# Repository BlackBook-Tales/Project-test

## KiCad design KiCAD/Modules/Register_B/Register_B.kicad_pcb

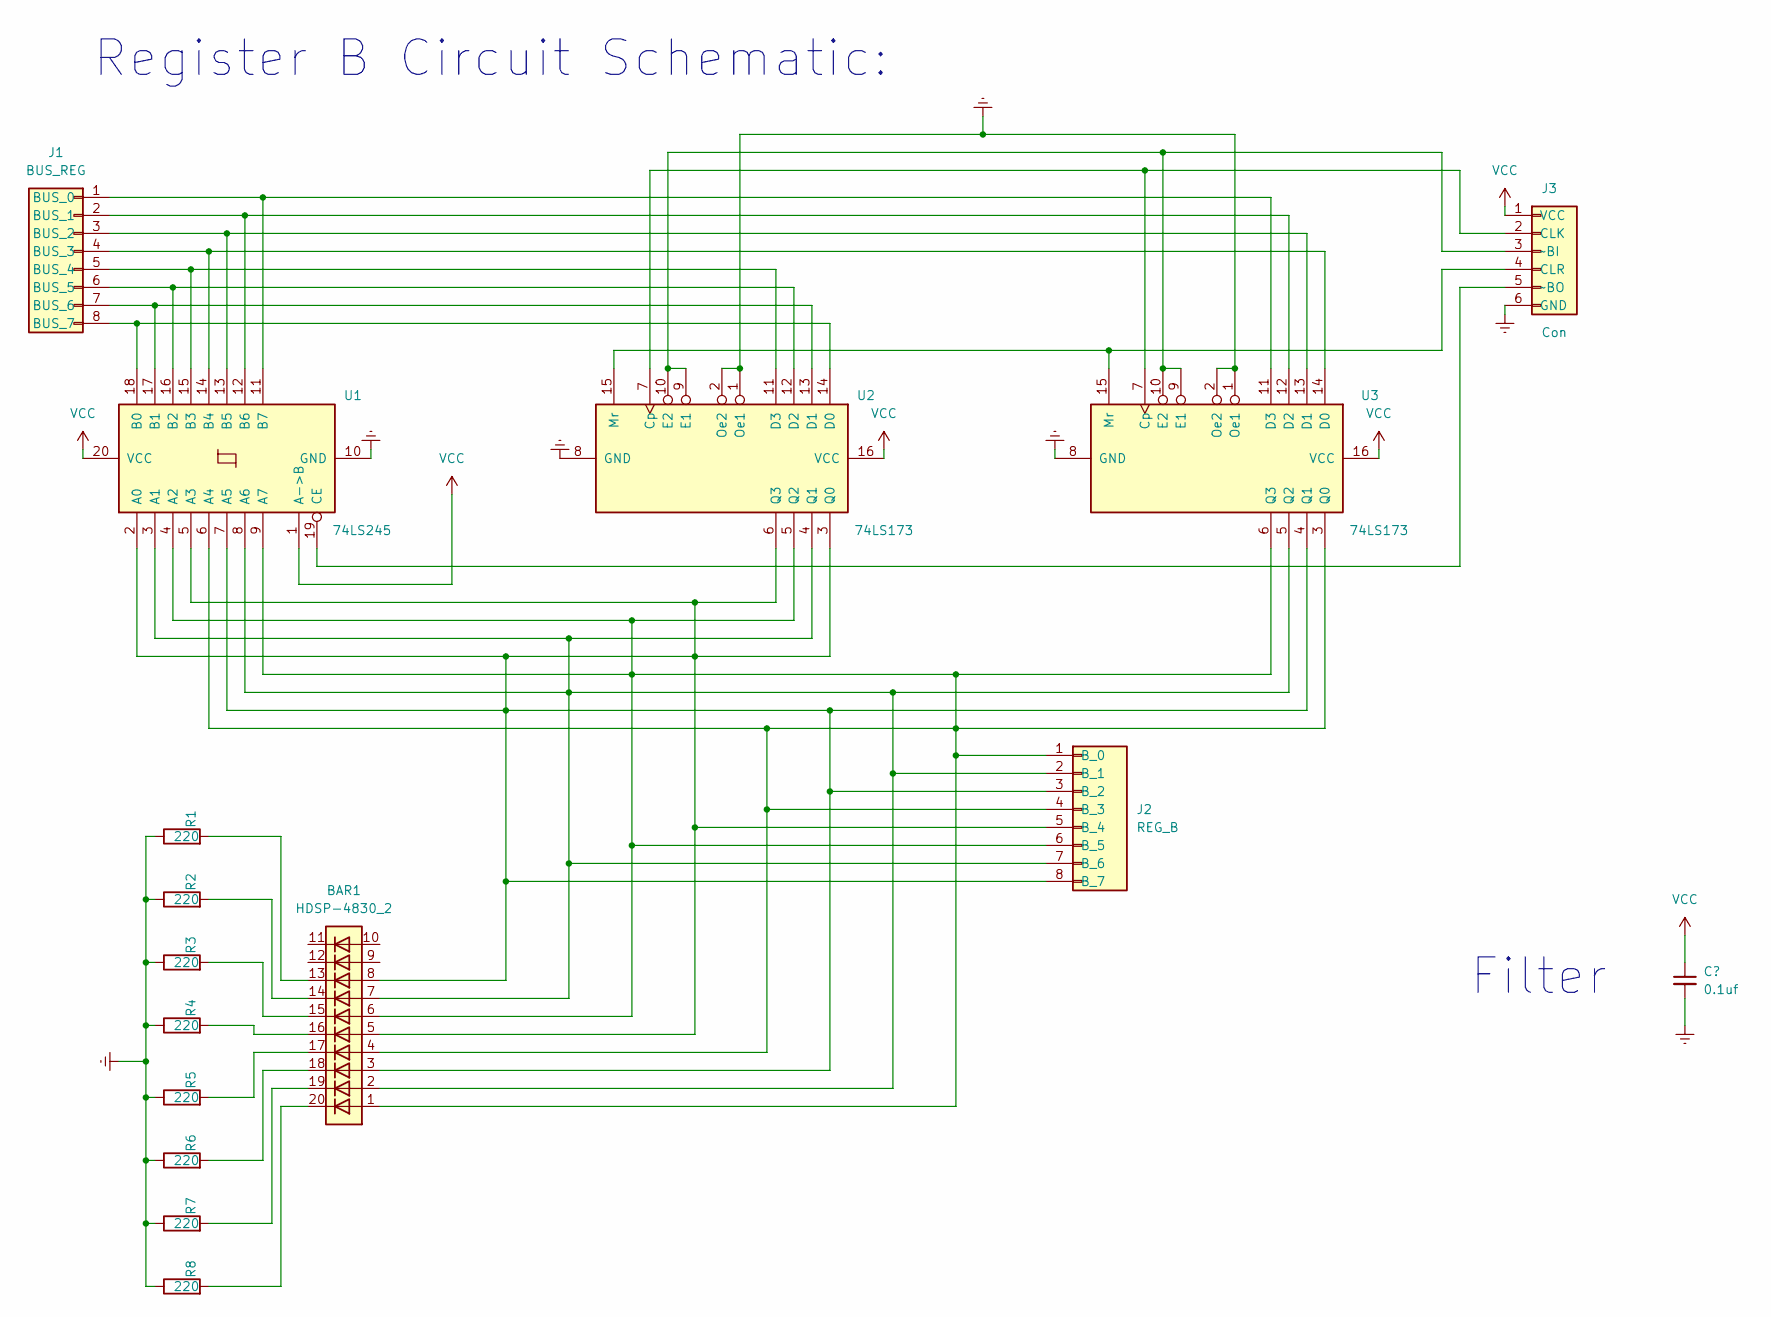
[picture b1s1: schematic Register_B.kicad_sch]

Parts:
BAR1: HDSP-4830_2; HDSP-4830
J1: BUS_REG; PinHeader_1x08_P1.00mm_Vertical
J2: REG_B; PinHeader_1x08_P1.00mm_Vertical
J3: Con; PinHeader_1x06_P1.00mm_Vertical
R1, R2, R3, R4, R5, R6, R7, R8: 220; R_Axial_DIN0204_L3.6mm_D1.6mm_P5.08mm_Horizontal
U1: 74LS245; DIP-20_W7.62mm
U2, U3: 74LS173; DIP-16_W7.62mm

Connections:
Earth: J3.6 (GND), R1.1, R2.1, R3.1, R4.1, R5.1, R6.1, R7.1, R8.1, U1.10 (GND), U2.1 (Oe1), U2.2 (Oe2), U2.8 (GND), U3.1 (Oe1), U3.2 (Oe2), U3.8 (GND)
unnamed: BAR1.1 (A), BAR1.4 (A), BAR1.6 (A), J2.1 (B_0), J2.4 (B_3), J2.6 (B_5), U1.4 (A2), U1.6 (A4), U1.9 (A7), U2.5 (Q2), U3.3 (Q0), U3.6 (Q3)
unnamed: BAR1.2 (A), BAR1.7 (A), J2.2 (B_1), J2.7 (B_6), U1.3 (A1), U1.8 (A6), U2.4 (Q1), U3.5 (Q2)
unnamed: BAR1.3 (A), BAR1.5 (A), BAR1.8 (A), J2.3 (B_2), J2.5 (B_4), J2.8 (B_7), U1.2 (A0), U1.5 (A3), U1.7 (A5), U2.3 (Q0), U2.6 (Q3), U3.4 (Q1)
unnamed: BAR1.13 (K), R1.2
unnamed: BAR1.14 (K), R2.2
unnamed: BAR1.15 (K), R3.2
unnamed: BAR1.16 (K), R4.2
unnamed: BAR1.17 (K), R5.2
unnamed: BAR1.18 (K), R6.2
unnamed: BAR1.19 (K), R7.2
unnamed: BAR1.20 (K), R8.2
unnamed: J1.1 (BUS_0), U1.11 (B7), U3.11 (D3)
unnamed: J1.2 (BUS_1), U1.12 (B6), U3.12 (D2)
unnamed: J1.3 (BUS_2), U1.13 (B5), U3.13 (D1)
unnamed: J1.4 (BUS_3), U1.14 (B4), U3.14 (D0)
unnamed: J1.5 (BUS_4), U1.15 (B3), U2.11 (D3)
unnamed: J1.6 (BUS_5), U1.16 (B2), U2.12 (D2)
unnamed: J1.7 (BUS_6), U1.17 (B1), U2.13 (D1)
unnamed: J1.8 (BUS_7), U1.18 (B0), U2.14 (D0)
unnamed: J3.2 (CLK), U2.7 (Cp), U3.7 (Cp)
unnamed: J3.3 (~BI), U2.9 (E1), U2.10 (E2), U3.9 (E1), U3.10 (E2)
unnamed: J3.4 (CLR), U2.15 (Mr), U3.15 (Mr)
unnamed: J3.5 (~BO), U1.19 (CE)
VCC: J3.1 (VCC), U1.1 (A->B), U1.20 (VCC), U2.16 (VCC), U3.16 (VCC)

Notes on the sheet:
Register B Circuit Schematic:
Filter

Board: 2 copper layers, 15 parts (0 on the bottom side), 25 nets, no tracks yet.

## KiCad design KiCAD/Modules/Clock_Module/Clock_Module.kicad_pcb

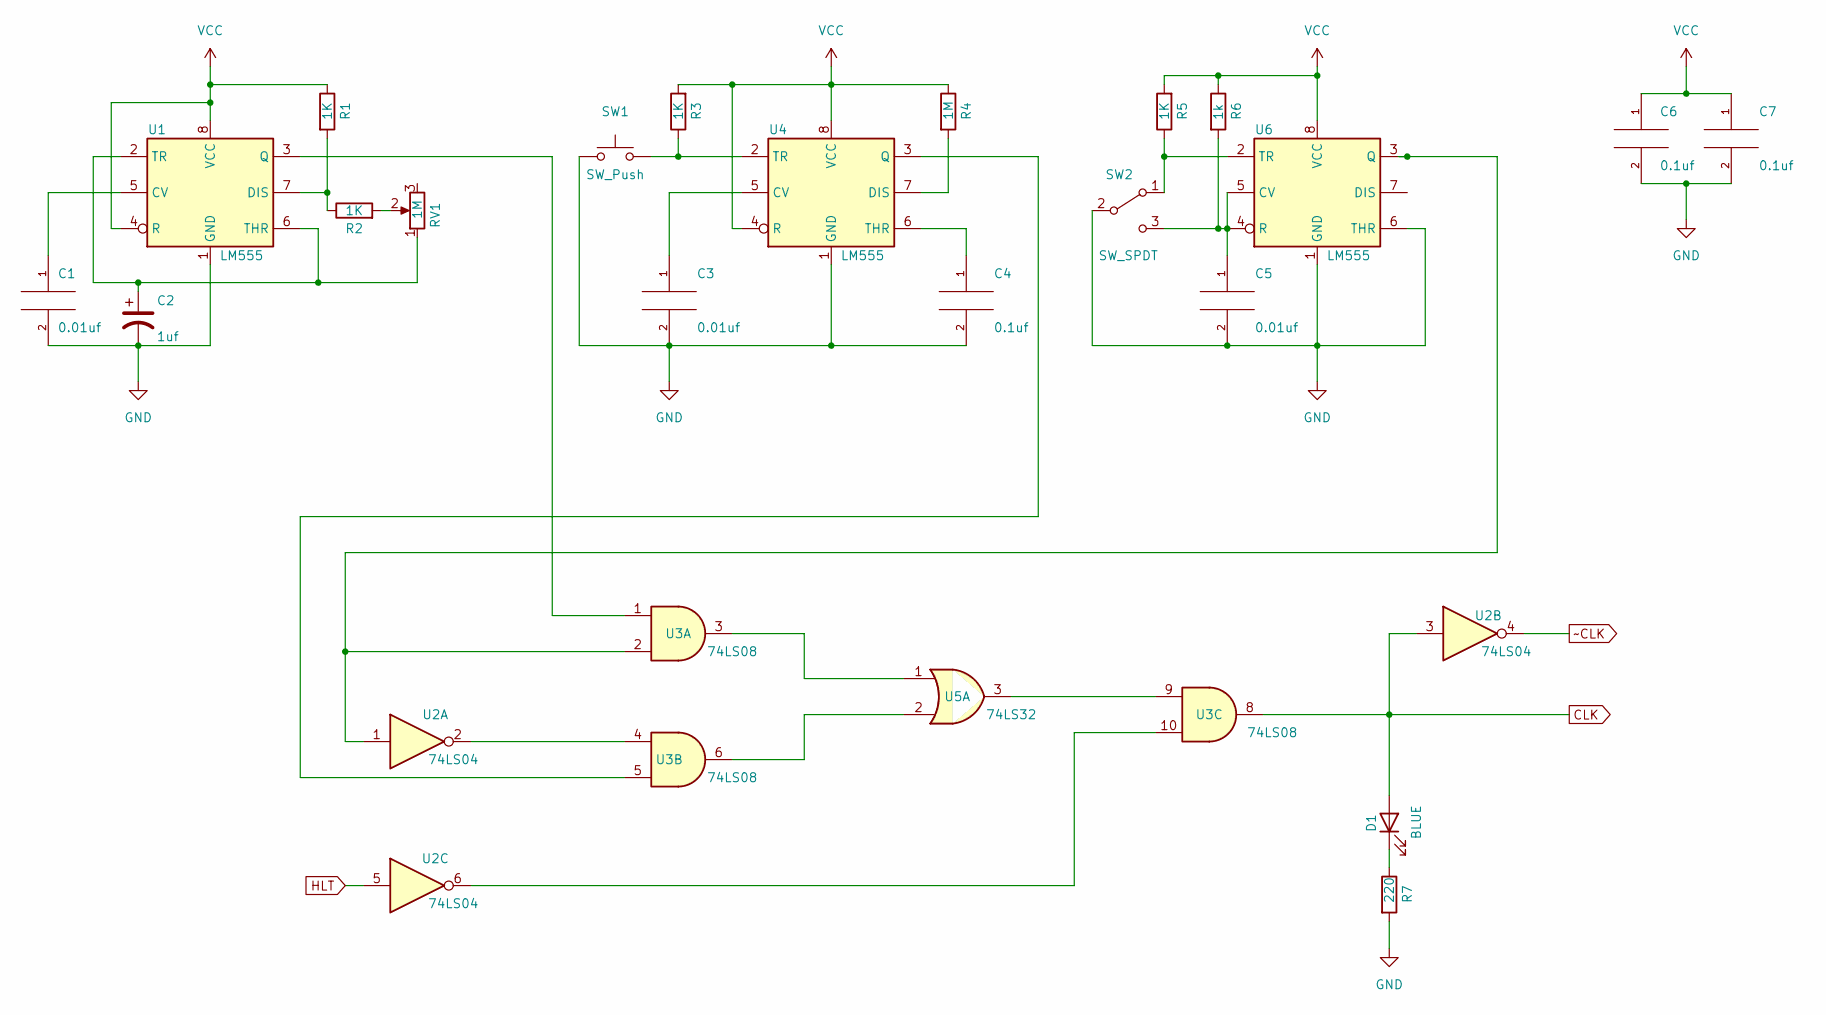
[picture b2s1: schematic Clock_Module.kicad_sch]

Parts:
C1, C3, C5: 0.01uf; C_Disc_D5.0mm_W2.5mm_P5.00mm
C2: 1uf; C_Radial_D5.0mm_H5.0mm_P2.00mm
C4, C6, C7: 0.1uf; C_Disc_D5.0mm_W2.5mm_P2.50mm
D1: BLUE; LED_D3.0mm_Horizontal_O3.81mm_Z10.0mm
R1, R2, R3, R5: 1K; R_Axial_DIN0204_L3.6mm_D1.6mm_P5.08mm_Horizontal
R4: 1M; R_Axial_DIN0204_L3.6mm_D1.6mm_P5.08mm_Horizontal
R6: 1k; R_Axial_DIN0204_L3.6mm_D1.6mm_P5.08mm_Horizontal
R7: 220; R_Axial_DIN0204_L3.6mm_D1.6mm_P5.08mm_Horizontal
RV1: 1M; Potentiometer_Alps_RK09L_Single_Vertical
SW1: SW_Push; SW_PUSH_6mm
SW2: SW_SPDT; SW_CuK_OS102011MA1QN1_SPDT_Angled
U1, U4, U6: LM555; DIP-8_W7.62mm
U2: 74LS04; DIP-14_W7.62mm
U3: 74LS08; DIP-14_W7.62mm
U5: 74LS32; DIP-14_W7.62mm

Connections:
unnamed: C1.1, U1.5 (CV)
unnamed: C2.1, RV1.1, U1.2 (TR), U1.6 (THR)
unnamed: C3.1, U4.5 (CV)
unnamed: C4.1, U4.6 (THR)
unnamed: C5.1, R6.2, SW2.3 (C), U6.4 (R), U6.5 (CV)
unnamed: D1.1 (K), R7.1
unnamed 6: D1.2 (A), U2.3, U3.8; also elsewhere on the board
unnamed 7: U2.5; also elsewhere on the board
unnamed: R1.2, R2.1, U1.7 (DIS)
unnamed: R2.2, RV1.2
unnamed: R3.1, SW1.2, U4.2 (TR)
unnamed: R4.2, U4.7 (DIS)
unnamed: R5.1, SW2.1 (A), U6.2 (TR)
unnamed: U1.3 (Q), U3.1
unnamed: U2.1, U3.2, U6.3 (Q)
unnamed: U2.2, U3.4
unnamed 16: U2.4; also elsewhere on the board
unnamed: U2.6, U3.10
unnamed: U3.3, U5.1
unnamed: U3.5, U4.3 (Q)
unnamed: U3.6, U5.2
unnamed: U3.9, U5.3
VCC: C6.1, C7.1, R1.1, R3.2, R4.1, R5.2, R6.1, U1.4 (R), U1.8 (VCC), U4.4 (R), U4.8 (VCC), U6.8 (VCC); also elsewhere on the board

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
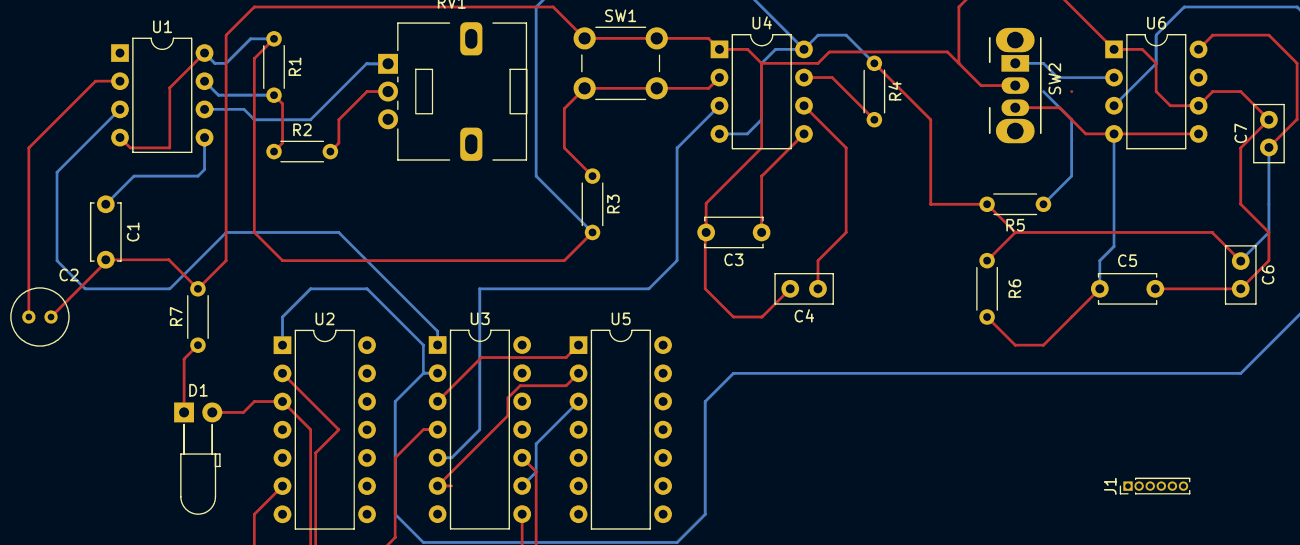
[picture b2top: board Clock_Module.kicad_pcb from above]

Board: 2 copper layers, 25 parts (0 on the bottom side), 25 nets.

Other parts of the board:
J1: Con; PinHeader_1x06_P1.00mm_Vertical

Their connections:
unnamed 6: J1.3 (CLK); also elsewhere on the board
unnamed 7: J1.4 (HLT); also elsewhere on the board
unnamed 16: J1.2 (~CLK); also elsewhere on the board
VCC: J1.1 (VCC); also elsewhere on the board

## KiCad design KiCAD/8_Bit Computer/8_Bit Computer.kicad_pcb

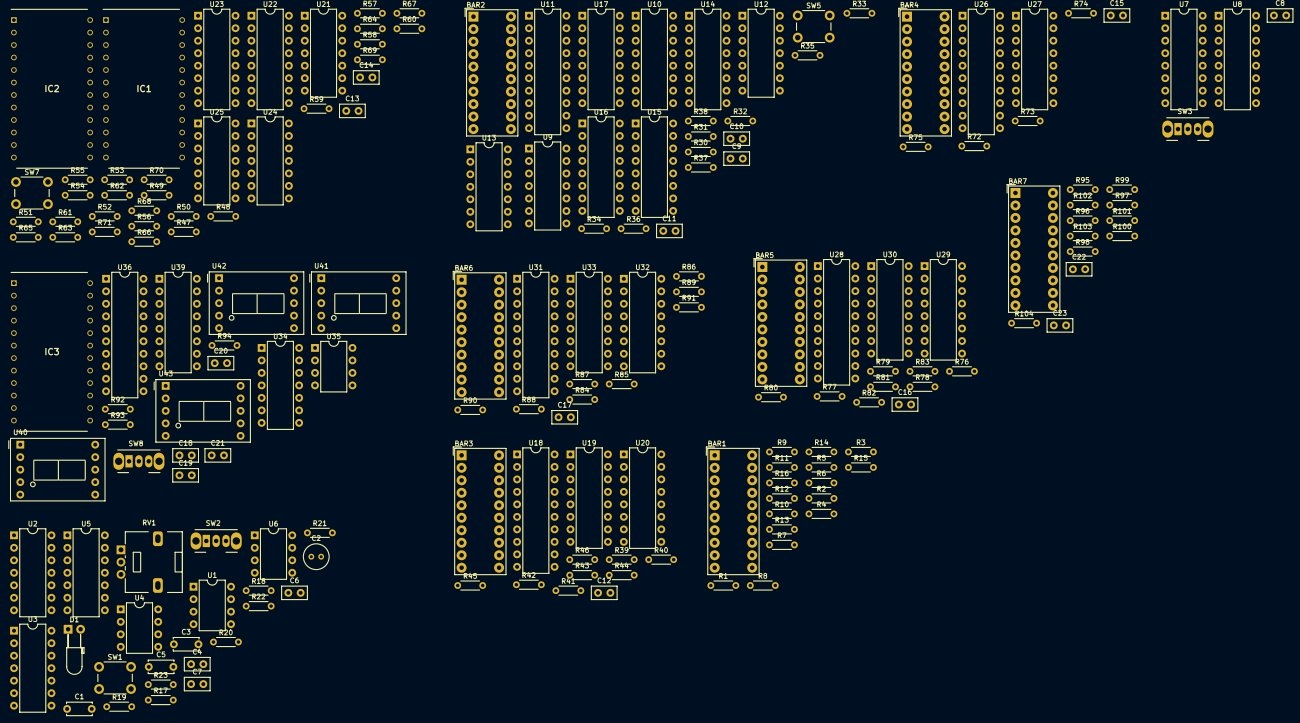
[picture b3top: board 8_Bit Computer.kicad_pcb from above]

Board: 2 copper layers, 180 parts (0 on the bottom side), 198 nets, no tracks yet.

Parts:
BAR1, BAR2, BAR3, BAR4, BAR5, BAR6, BAR7: HDSP-4830_2; HDSP-4830
C1, C3, C5: C_Disc_D5.0mm_W2.5mm_P5.00mm
C2: C_Radial_D5.0mm_H5.0mm_P2.00mm
C4, C6, C7: C_Disc_D5.0mm_W2.5mm_P2.50mm
C8, C10, C11, C12, C13, C14, C15, C16, C17, C20, C21, C22, C23: 0.1uf; C_Disc_D5.0mm_W2.5mm_P2.50mm
C9, C18, C19: 0.01uf; C_Disc_D5.0mm_W2.5mm_P2.50mm
D1: LED_D3.0mm_Horizontal_O3.81mm_Z10.0mm
IC1, IC2, IC3: AT28C16-15PI; DIP1550W56P254L3190H559Q24N
R1, R2, R3, R4, R5, R6, R7, R8, R92: 10K; R_Axial_DIN0204_L3.6mm_D1.6mm_P5.08mm_Horizontal
R9, R10, R11, R12, R13, R14, R15, R16, R31, R32, R33, R34, R35, R36, R37, R38, R39, R40, R41, R42, R43, R44, R45, R46, R48, R49, R50, R51, R52, R53, R54, R55, R56, R57, R58, R59, R60, R61, R62, R63, R64, R65, R66, R67, R68, R69, R70, R71, R72, R73, R74, R75, R76, R77, R78, R79, R80, R81, R82, R83, R84, R85, R86, R87, R88, R89, R90, R91, R95, R96, R97, R98, R99, R100, R101, R102, R103, R104: 220; R_Axial_DIN0204_L3.6mm_D1.6mm_P5.08mm_Horizontal
R17, R18, R19, R20, R21, R22, R23: R_Axial_DIN0204_L3.6mm_D1.6mm_P5.08mm_Horizontal
R30, R47, R94: 1K; R_Axial_DIN0204_L3.6mm_D1.6mm_P5.08mm_Horizontal
R93: 100K; R_Axial_DIN0204_L3.6mm_D1.6mm_P5.08mm_Horizontal
RV1: Potentiometer_Alps_RK09L_Single_Vertical
SW1: SW_PUSH_6mm
SW2: SW_CuK_OS102011MA1QN1_SPDT_Angled
SW3, SW8: SW_SPDT; SW_CuK_OS102011MA1QN1_SPDT_Angled
SW5, SW7: SW_Push; SW_PUSH_6mm
U1, U4, U6: DIP-8_W7.62mm
U2, U3, U5: DIP-14_W7.62mm
U7, U19, U20, U29, U30, U32, U33: 74LS173; DIP-16_W7.62mm
U8, U10, U14, U15: 74LS157; DIP-16_W7.62mm
U9, U21: 74LS00; DIP-14_W7.62mm
U11, U18, U26, U28, U31: 74LS245; DIP-20_W7.62mm
U12, U13, U24, U25: 74LS04; DIP-14_W7.62mm
U16, U17: 74189; DIP-16_W7.62mm
U22, U27: 74LS161; DIP-16_W7.62mm
U23: 74LS138; DIP-16_W7.62mm
U34: 74LS08; DIP-14_W7.62mm
U35: LM555xN; DIP-8_W7.62mm
U36: 74LS273; DIP-20_W7.62mm
U39: 74LS139; DIP-16_W7.62mm
U40, U41, U42, U43: D168K; D1X8K

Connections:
/Sheet: A Register/A_0: BAR5.1 (A), BAR5.4 (A), BAR5.6 (A), U28.4 (A2), U28.6 (A4), U28.9 (A7), U29.5 (Q2), U30.3 (Q0), U30.6 (Q3)
/Sheet: A Register/A_1: BAR5.2 (A), BAR5.7 (A), U28.3 (A1), U28.8 (A6), U29.4 (Q1), U30.5 (Q2)
/Sheet: A Register/A_2: BAR5.3 (A), BAR5.5 (A), BAR5.8 (A), U28.2 (A0), U28.5 (A3), U28.7 (A5), U29.3 (Q0), U29.6 (Q3), U30.4 (Q1)
/Sheet: A Register/BUS_0: BAR1.1 (A), R8.2, U7.11 (D3), U11.11 (B7), U15.13 (I1d), U18.11 (B7), U20.11 (D3), U26.9 (A7), U27.3 (D0), U28.11 (B7), U30.11 (D3), U31.11 (B7), U33.11 (D3)
/Sheet: A Register/BUS_1: BAR1.2 (A), R7.2, U7.12 (D2), U11.12 (B6), U15.10 (I1c), U18.12 (B6), U20.12 (D2), U26.8 (A6), U27.4 (D1), U28.12 (B6), U30.12 (D2), U31.12 (B6), U33.12 (D2)
/Sheet: A Register/BUS_2: BAR1.4 (A), R5.2, U7.14 (D0), U11.14 (B4), U15.3 (I1a), U18.14 (B4), U20.14 (D0), U26.6 (A4), U27.6 (D3), U28.13 (B5), U30.13 (D1), U31.14 (B4), U33.14 (D0)
/Sheet: A Register/BUS_3: BAR1.5 (A), R4.2, U11.15 (B3), U14.10 (I1d), U18.15 (B3), U19.11 (D3), U28.14 (B4), U30.14 (D0), U31.15 (B3), U32.11 (D3)
/Sheet: A Register/BUS_4: BAR1.6 (A), R3.2, U11.16 (B2), U14.13 (I1c), U18.16 (B2), U19.12 (D2), U28.15 (B3), U28.16 (B2), U29.11 (D3), U29.12 (D2), U31.16 (B2), U32.12 (D2)
/Sheet: A Register/BUS_6: BAR1.7 (A), R2.2, U11.17 (B1), U14.6 (I1b), U18.17 (B1), U19.13 (D1), U28.17 (B1), U29.13 (D1), U31.17 (B1), U32.13 (D1)
/Sheet: A Register/BUS_7: BAR1.8 (A), R1.2, U11.18 (B0), U14.3 (I1a), U18.18 (B0), U19.14 (D0), U28.18 (B0), U29.14 (D0), U31.18 (B0), U32.14 (D0)
/Sheet: A Register/CLK: C9.2, D1.2 (A), U2.3, U3.8, U7.7 (Cp), U19.7 (Cp), U20.7 (Cp), U27.2 (CP), U29.7 (Cp), U30.7 (Cp), U32.7 (Cp), U33.7 (Cp)
/Sheet: A Register/CLR: U7.15 (Mr), U9.11, U19.15 (Mr), U20.15 (Mr), U29.15 (Mr), U30.15 (Mr), U32.15 (Mr), U33.15 (Mr)
/Sheet: A Register/~AI: U13.10, U29.9 (E1), U29.10 (E2), U30.9 (E1), U30.10 (E2)
/Sheet: A Register/~AO: U13.12, U28.19 (CE)
/Sheet: ALU/BUS_2: BAR1.3 (A), R6.2, U7.13 (D1), U11.13 (B5), U15.6 (I1b), U18.13 (B5), U20.13 (D1), U26.7 (A5), U27.5 (D2), U31.13 (B5), U33.13 (D1)
/Sheet: ALU/B_0: BAR6.1 (A), BAR6.2 (A), BAR6.3 (A), BAR6.4 (A), BAR6.5 (A), BAR6.6 (A), BAR6.7 (A), BAR6.8 (A), U31.2 (A0), U31.3 (A1), U31.4 (A2), U31.5 (A3), U31.6 (A4), U31.7 (A5), U31.8 (A6), U31.9 (A7), U32.3 (Q0), U32.4 (Q1), U32.5 (Q2), U32.6 (Q3), U33.3 (Q0), U33.4 (Q1), U33.5 (Q2), U33.6 (Q3)
/Sheet: ALU/CF: IC1.23 (A8), IC2.23 (A8)
/Sheet: ALU/ZF: IC1.22 (A9), IC2.22 (A9)
/Sheet: B Register/~BI: U25.4, U32.9 (E1), U32.10 (E2), U33.9 (E1), U33.10 (E2)
/Sheet: Clock/HLT: IC2.17 (I/O7), U2.5
/Sheet: Clock/~CLK: U2.4, U22.2 (CP)
/Sheet: Control Logic/CE: IC1.13 (I/O3), U27.7 (CEP), U27.10 (CET)
/Sheet: Control Logic/IR_4: BAR3.3 (A), BAR3.5 (A), BAR3.8 (A), IC1.2 (A6), IC1.5 (A3), IC2.2 (A6), IC2.5 (A3), U18.2 (A0), U18.5 (A3), U18.7 (A5), U19.3 (Q0), U19.6 (Q3), U20.4 (Q1)
/Sheet: Control Logic/IR_5: BAR3.1 (A), BAR3.4 (A), BAR3.6 (A), IC1.4 (A4), IC2.4 (A4), U18.4 (A2), U18.6 (A4), U18.9 (A7), U19.5 (Q2), U20.3 (Q0), U20.6 (Q3)
/Sheet: Control Logic/IR_6: BAR3.2 (A), BAR3.7 (A), IC1.3 (A5), IC2.3 (A5), U18.3 (A1), U18.8 (A6), U19.4 (Q1), U20.5 (Q2)
/Sheet: Control Logic/OI: IC1.14 (I/O4), U34.1
/Sheet: Control Logic/RI: IC2.15 (I/O5), U9.2
/Sheet: Control Logic/~CLR: U9.4, U9.8, U9.12, U9.13, U27.1 (~MR), U36.1 (~Mr)
/Sheet: Control Logic/~CO: U24.6, U26.19 (CE)
/Sheet: Control Logic/~II: U13.8, U19.9 (E1), U19.10 (E2), U20.9 (E1), U20.10 (E2)
/Sheet: Control Logic/~IO: U13.6, U18.19 (CE)
/Sheet: Control Logic/~J: U24.8, U27.9 (~PE)
/Sheet: Control Logic/~MI: U7.9 (E1), U7.10 (E2), U24.2
/Sheet: Control Logic/~RO: U11.19 (CE), U24.4
/Sheet: MAR/A_0: U8.12 (Zd), U16.1 (A0), U17.1 (A0)
/Sheet: MAR/A_1: U8.9 (Zc), U16.15 (A1), U17.15 (A1)
/Sheet: MAR/A_2: U8.7 (Zb), U16.14 (A2), U17.14 (A2)
/Sheet: MAR/A_3: U8.4 (Za), U16.13 (A3), U17.13 (A3)
/Sheet: MAR/PROG: SW3.1 (A), U8.1 (S), U10.1 (S), U14.1 (S), U15.1 (S)
Earth: C6.2, C7.2, C8.2, C12.2, C15.2, C16.2, C17.2, C18.2, C19.2, C22.2, C23.2, IC1.12 (GND), IC1.18 (~CE), IC1.19 (A10), IC1.20 (~OE), IC2.1 (A7), IC2.12 (GND), IC2.18 (~CE), IC2.19 (A10), IC2.20 (~OE), IC3.12 (GND), IC3.18 (~CE), IC3.20 (~OE), R1.1, R2.1, R3.1, R4.1, R5.1, R6.1, R7.1, R8.1, R9.1, R10.1, R11.1, R12.1, R13.1, R14.1, R15.1, R16.1, R30.1, R31.1, R32.1, R33.1, R34.1, R35.1, R36.1, R37.1, R38.1, R39.1, R40.1, R41.1, R42.1, R43.1, R44.1, R45.1, R46.1, R47.1, R53.1, R54.1, R55.1, R56.1, R57.1, R58.1, R59.1, R60.1, R61.1, R62.1, R63.1, R64.1, R65.1, R66.1, R67.1, R68.1, R69.1, R70.1, R71.1, R72.1, R73.1, R74.1, R75.1, R76.1, R77.1, R78.1, R79.1, R80.1, R81.1, R82.1, R83.1, R84.1, R85.1, R86.1, R87.1, R88.1, R89.1, R90.1, R91.1, R92.1, R95.2, R96.2, R97.1, R98.1, R99.1, R100.1, R101.1, R102.1, R103.1, R104.1, SW3.2 (B), SW5.1, U7.1 (Oe1), U7.2 (Oe2), U7.8 (GND), U8.8 (GND), U8.15 (E), U10.8 (GND), U10.15 (E), U11.10 (GND), U14.8 (GND), U14.15 (E), U15.8 (GND), U15.15 (E), U16.2 (~CS), U16.8 (GND), U17.2 (~CS), U17.8 (GND), U18.10 (GND), U19.1 (Oe1), U19.2 (Oe2), U19.8 (GND), U20.1 (Oe1), U20.2 (Oe2), U20.8 (GND), U22.8 (GND), U23.4 (E1), U23.5 (E2), U23.8 (GND), U26.1 (A->B), U26.10 (GND), U27.8 (GND), U28.10 (GND), U29.1 (Oe1), U29.2 (Oe2), U29.8 (GND), U30.1 (Oe1), U30.2 (Oe2), U30.8 (GND), U31.10 (GND), U32.1 (Oe1), U32.2 (Oe2), U32.8 (GND), U33.1 (Oe1), U33.2 (Oe2), U33.8 (GND), U35.1 (GND), U36.10 (GND), U39.1 (E)
GND: C1.2, C2.2, C3.2, C4.2, C5.2, C10.2, C11.2, C13.2, C14.2, C20.2, C21.2, R23.2, SW1.1, SW2.2 (B), U1.1 (GND), U4.1 (GND), U6.1 (GND), U6.6 (THR)
unnamed: BAR1.13 (K), R9.2
unnamed: BAR1.14 (K), R10.2
unnamed: BAR1.15 (K), R11.2
unnamed: BAR1.16 (K), R12.2
unnamed: BAR1.17 (K), R13.2
unnamed: BAR1.18 (K), R14.2
unnamed: BAR1.19 (K), R15.2
unnamed: BAR1.20 (K), R16.2
unnamed: BAR2.1 (A), U11.9 (A7), U13.4
unnamed: BAR2.2 (A), U11.8 (A6), U13.2
unnamed: BAR2.3 (A), U11.7 (A5), U12.12
unnamed: BAR2.4 (A), U11.6 (A4), U12.10
unnamed: BAR2.5 (A), U11.5 (A3), U12.8
unnamed: BAR2.6 (A), U11.4 (A2), U12.6
unnamed: BAR2.7 (A), U11.3 (A1), U12.4
unnamed: BAR2.8 (A), U11.2 (A0), U12.2
unnamed: BAR2.13 (K), R31.2
unnamed: BAR2.14 (K), R32.2
unnamed: BAR2.15 (K), R33.2
unnamed: BAR2.16 (K), R34.2
unnamed: BAR2.17 (K), R35.2
unnamed: BAR2.18 (K), R36.2
unnamed: BAR2.19 (K), R37.2
unnamed: BAR2.20 (K), R38.2
unnamed: BAR3.13 (K), R39.2
unnamed: BAR3.14 (K), R40.2
unnamed: BAR3.15 (K), R41.2
unnamed: BAR3.16 (K), R42.2
unnamed: BAR3.17 (K), R43.2
unnamed: BAR3.18 (K), R44.2
unnamed: BAR3.19 (K), R45.2
unnamed: BAR3.20 (K), R46.2
unnamed: BAR4.1 (A), U26.14 (B4), U27.11 (Q3)
unnamed: BAR4.2 (A), U26.13 (B5), U27.12 (Q2)
unnamed: BAR4.3 (A), U26.12 (B6), U27.13 (Q1)
unnamed: BAR4.4 (A), U26.11 (B7), U27.14 (Q0)
unnamed: BAR4.17 (K), R75.2
unnamed: BAR4.18 (K), R74.2
unnamed: BAR4.19 (K), R73.2
unnamed: BAR4.20 (K), R72.2
unnamed: BAR5.13 (K), R76.2
unnamed: BAR5.14 (K), R77.2
unnamed: BAR5.15 (K), R78.2
unnamed: BAR5.16 (K), R79.2
unnamed: BAR5.17 (K), R80.2
unnamed: BAR5.18 (K), R81.2
unnamed: BAR5.19 (K), R82.2
unnamed: BAR5.20 (K), R83.2
unnamed: BAR6.13 (K), R84.2
unnamed: BAR6.14 (K), R85.2
unnamed: BAR6.15 (K), R86.2
unnamed: BAR6.16 (K), R87.2
unnamed: BAR6.17 (K), R88.2
unnamed: BAR6.18 (K), R89.2
unnamed: BAR6.19 (K), R90.2
unnamed: BAR6.20 (K), R91.2
unnamed: BAR7.7 (A), BAR7.8 (A)
unnamed: BAR7.13 (K), R97.2
unnamed: BAR7.14 (K), R98.2
unnamed: BAR7.15 (K), R99.2
unnamed: BAR7.16 (K), R100.2
unnamed: BAR7.17 (K), R101.2
unnamed: BAR7.18 (K), R102.2
unnamed: BAR7.19 (K), R103.2
unnamed: BAR7.20 (K), R104.2
unnamed: C1.1, U1.5 (CV)
unnamed: C2.1, RV1.1, U1.2 (TR), U1.6 (THR)
unnamed: C3.1, U4.5 (CV)
unnamed: C4.1, U4.6 (THR)
unnamed: C5.1, R22.2, SW2.3 (C), U6.4 (R), U6.5 (CV)
unnamed: C9.1, R30.2, U9.1
unnamed: C18.1, R93.2, U35.2 (TR), U35.6 (THR)
unnamed: C19.1, U35.5 (CV)
unnamed: D1.1 (K), R23.1
unnamed: IC1.8 (A0), IC2.8 (A0), U23.1 (A0)
unnamed: IC1.7 (A1), IC2.7 (A1), U23.2 (A1)
unnamed: IC1.6 (A2), IC2.6 (A2), U23.3 (A2)
unnamed: IC2.16 (I/O6), U24.1
unnamed: IC2.14 (I/O4), U24.3
unnamed: IC2.13 (I/O3), U13.5
unnamed: IC2.11 (I/O2), U13.9
unnamed: IC2.10 (I/O1), U13.11
unnamed: IC2.9 (I/O0), U13.13
unnamed: IC1.17 (I/O7), U25.1
unnamed: IC1.15 (I/O5), U25.3
unnamed: IC1.11 (I/O2), U24.5
unnamed: IC1.10 (I/O1), U24.9
unnamed: IC1.9 (I/O0), U24.11
unnamed: IC3.1 (A7), U36.19 (Q7)
unnamed: IC3.2 (A6), U36.16 (Q6)
unnamed: IC3.3 (A5), U36.15 (Q5)
unnamed: IC3.4 (A4), U36.12 (Q4)
unnamed: IC3.5 (A3), U36.9 (Q3)
unnamed: IC3.6 (A2), U36.6 (Q2)
unnamed: IC3.7 (A1), U36.5 (Q1)
unnamed: IC3.8 (A0), U36.2 (Q0)
unnamed: IC3.9 (I/O0), U40.10 (G), U41.10 (G), U42.10 (G), U43.10 (G)
unnamed: IC3.10 (I/O1), U40.9 (F), U41.9 (F), U42.9 (F), U43.9 (F)
unnamed: IC3.11 (I/O2), U40.1 (E), U41.1 (E), U42.1 (E), U43.1 (E)
unnamed: IC3.13 (I/O3), U40.2 (D), U41.2 (D), U42.2 (D), U43.2 (D)
unnamed: IC3.14 (I/O4), U40.4 (C), U41.4 (C), U42.4 (C), U43.4 (C)
unnamed: IC3.15 (I/O5), U40.6 (B), U41.6 (B), U42.6 (B), U43.6 (B)
unnamed: IC3.16 (I/O6), U40.7 (A), U41.7 (A), U42.7 (A), U43.7 (A)
unnamed: IC3.17 (I/O7), U40.5 (DP), U41.5 (DP), U42.5 (DP), U43.5 (DP)
unnamed: IC3.19 (A10), SW8.2 (B)
unnamed: IC3.22 (A9), U39.3 (A1)
unnamed: IC3.23 (A8), U39.2 (A0)
unnamed: R17.2, R18.1, U1.7 (DIS)
unnamed: R18.2, RV1.2
unnamed: R19.1, SW1.2, U4.2 (TR)
unnamed: R20.2, U4.7 (DIS)
unnamed: R21.1, SW2.1 (A), U6.2 (TR)
unnamed: R47.2, SW7.2, U9.9, U9.10
unnamed: R92.2, SW8.1 (A)
unnamed: R93.1, R94.1, U35.7 (DIS)
unnamed: U8.11 (I0c), U8.14 (I0d)
unnamed: SW5.2, U10.14 (I0d)
unnamed: U1.3 (Q), U3.1
unnamed: U2.1, U3.2, U6.3 (Q)
unnamed: U2.2, U3.4
unnamed: U2.6, U3.10
unnamed: U3.3, U5.1
unnamed: U3.5, U4.3 (Q)
unnamed: U3.6, U5.2
unnamed: U3.9, U5.3
unnamed: U7.3 (Q0), U8.3 (I1a)
unnamed: U7.4 (Q1), U8.6 (I1b)
unnamed: U7.5 (Q2), U8.13 (I1d)
unnamed: U7.6 (Q3), U8.10 (I1c)
unnamed: U10.9 (Zc), U16.3 (~WE), U17.3 (~WE)
unnamed: U9.3, U10.13 (I1d)
unnamed: U12.1, U16.5 (~01)
unnamed: U12.3, U16.7 (~02)
unnamed: U12.5, U16.9 (~03)
unnamed: U12.9, U16.11 (~04)
unnamed: U12.11, U17.11 (~04)
unnamed: U12.13, U17.9 (~03)
unnamed: U13.1, U17.7 (~02)
unnamed: U13.3, U17.5 (~01)
unnamed: U14.4 (Za), U16.4 (D1)
unnamed: U14.7 (Zb), U16.6 (D2)
unnamed: U14.9 (Zc), U16.10 (D3)
unnamed: U14.12 (Zd), U16.12 (D4)
unnamed: U15.4 (Za), U17.12 (D4)
unnamed: U15.7 (Zb), U17.10 (D3)
unnamed: U15.9 (Zc), U17.6 (D2)
unnamed: U15.12 (Zd), U17.4 (D1)
unnamed: U9.6, U21.1, U21.2
unnamed: U21.3, U22.1 (~MR)
unnamed: U9.5, U23.10 (O5)
unnamed: U34.3, U36.11 (Cp)
unnamed: U34.5, U34.8
unnamed: U39.4 (O0), U43.3 (CC), U43.8 (CC)
unnamed: U39.5 (O1), U42.3 (CC), U42.8 (CC)
unnamed: U39.6 (O2), U41.3 (CC), U41.8 (CC)
unnamed: U39.7 (O3), U40.3 (CC), U40.8 (CC)
VCC: C6.1, C7.1, C8.1, C10.1, C11.1, C12.1, C13.1, C14.1, C15.1, C16.1, C17.1, C20.1, C21.1, C22.1, C23.1, IC1.1 (A7), IC1.21 (~WE), IC1.24 (VCC), IC2.21 (~WE), IC2.24 (VCC), IC3.21 (~WE), IC3.24 (VCC), R17.1, R19.2, R20.1, R21.2, R22.1, R48.2, R49.2, R50.2, R51.2, R52.2, R94.2, SW7.1, SW8.3 (C), U1.4 (R), U1.8 (VCC), U4.4 (R), U4.8 (VCC), U6.8 (VCC), U7.16 (VCC), U8.16 (VCC), U10.16 (VCC), U11.1 (A->B), U11.20 (VCC), U14.16 (VCC), U15.16 (VCC), U16.16 (VCC), U17.16 (VCC), U18.1 (A->B), U18.20 (VCC), U19.16 (VCC), U20.16 (VCC), U22.7 (CEP), U22.9 (~PE), U22.10 (CET), U22.16 (VCC), U23.6 (E3), U23.16 (VCC), U26.20 (VCC), U27.16 (VCC), U28.1 (A->B), U28.20 (VCC), U29.16 (VCC), U30.16 (VCC), U31.1 (A->B), U31.19 (CE), U31.20 (VCC), U32.16 (VCC), U33.16 (VCC), U35.8 (VCC)

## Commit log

2023-02-22 Second commit
